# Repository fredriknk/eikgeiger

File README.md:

# EIKGEIGER

Eikgeiger opensource project for detection of background radiation in Norway. It is developed in cooperation with Eik Ideverksted. Use the design for anything you like comercially and privately, but i would love if you fork it so i can see what it is used for.

## First Batch
Thanks to [PCBway](www.pcbway.com) for providing assembled prototype units for this project. Its awesome that you support the opensource community like this! If you want one for yourself, i've made a [pcbway project](https://www.pcbway.com/project/shareproject/EikGeiger_IOT_Geigercounter_60bd1e1f.html) which you can make an assembly order quite easily. 

## Description
It uses an[ESP32-WROOM-32E](./DOCUMENTATION/esp32-wroom-32e_esp32-wroom-32ue_datasheet_en.pdf) wifi module both communication and MCU, and is mostly based on surface mount components.

Thanks to the DIYgeiger radmon project for inspiration [DIYGeiger RADMON + kit](https://sites.google.com/site/diygeigercounter/home/gk-radmon).

If you want to handsolder this, i really recommend to check out the awesome IBOM assembly utility (use it with a desktop as it sucks on mobile)
[Assembly IBOM](https://htmlpreview.github.io/?https://raw.githubusercontent.com/fredriknk/eikgeiger/main/PRODUCTION/eikgeiger-ibom.html)

[SCHEMATIC](./DOCUMENTATION/Opengieger_schematic.pdf)
## Specifications
| **Parameter**     | **Description**                                                     |
|-------------------|---------------------------------------------------------------------|
| _Input voltage_   | Usb-C cable, Header 4-6v, Direct 3.3v                               |
| _Current_         | Wifi: 150-250mA, Radio Off: 44mA, Only HV psup 4mA, Deep sleep 70uA |
| _Communication_   | 2.4ghz WIFI, Uart TTL, Uart over USB                                |
| _Baudrate_        | 115200                                                              |
| _PCB size_        | 31x119mm                                                            |
| _Case size_       | 30x35x121mm                                                         |
| _Series Resistor_ | 4.51MOHM                                                         |

## Serial port controll comands

To reconfigure device settings you need to connect the eikgeiger to a computer with a serial terminal (I reccomend to just use the [Arduino Program](https://www.arduino.cc/en/software), but any serial terminal should work)

When you want to configure a value you use two characters plus a number. So to set the PWM frequency to 2000hz, you would write PF2000 in the terminal and send. Some commands need a specific number, eg to factory reset you must transmit FR9999. after you have verified that the configuraion works you use SA1 to save the config to the flash eeprom

| **Characters**| **Unit**                | **Value** | **Factory Value** | **Description**                                                                                                                                                                                                                                           | **Example** |
|---------------|-------------------------|-----------|-------------------|-----------------------------------------------------------------------------------------------------------------------------------------------------------------------------------------------------------------------------------------------------------|-------------|
| VO            | _VOLT (value/4096 %)_   | 0-2000    | 350               | Set pwm duty cycle, this is a value which controlls the duty cycle of HV power supply, it is a 12bit (4096) value, but you cant go over 50% or the coil field colapses. So keep it under 2046=50% duty cycle. (SBM-20 tubes like it best between 350-400) | VO350       |
| VF            | _FREQUENCY (hz)_        | 0-18000   | 1001              | Set pwm frequency, from experimentation i have found ~1000hz to be most effective but it can make some coil whine, It is smart to not have this as a value divisible by log output, or it might generate some interferance with ADC readings              | VF1001      |
| SA            | _SAVE_                  | 1         | -                 | Saves parameters to eeprom                                                                                                                                                                                                                                | SA1         |
| RE            | _RESTART_               | 1         | -                 | Restarts device                                                                                                                                                                                                                                           | RE1         |
| RF            | _FACTORY RESET_         | 9999/1111 | -                 | Resets all values to factory default and restarts device, 1111 will reset all settings except wifi and radmon credentials, 9999 resets everything                                                                                                         | RF9999      |
| BE            | _BEEPER (activation)_   | 0/1       | 0                 | Activate beeper output 0=Off 1=On                                                                                                                                                                                                                         | BE1         |
| BD            | _BEEPER duty (val/255) _| 0-127     | 50                | Beeper duty cycle, higher number is louder                                                                                                                                                                                                                | BD50        |
| BF            | _BEEPER FREQUENCY (hz)_ | 10-40000  | 6000              | Beeper frequency 6000hZ is a very nice and annoying frequency                                                                                                                                                                                             | BF6000      |
| LE            | _LED (activation)_      | 0/1       | 1                 | Activate LED output 0=Off 1=On                                                                                                                                                                                                                            | LE1         |
| LF            | _FLASHTIME (mS)_        | 1-500     | 10                | How long the beeper beeps and led flashes in mS for every click. If value is higher than 60*1000/CPM, you will have counts without indication                                                                                                             | LF10        |
| LO            | _LOG OUTPUT_            | 0/1       | 1                 | Outputs  raw_volt:(Voltage ADC reading, arbtrary number not directly related to volt) set_volt:(Duty cycle value) cpmM:(Running average CPM for one minute) cpmH:(Running average CPM for one hour) cpm:(CPM value for last detection)                    | LO1         |
| LS            | _LOG SPEED_             | 0-10000   | 1000              | Number of milliseconds for every log output over serial    																																							                                      | LS1000      |
| EV            | _EVENTS (number)_       | 0-1000    | 0                 | How many events for one flash, in practice it will divide by that number, so a value of 10, it will need 10 detections for every led and ticker flash.                                                                                                    | EV0         |

## Description
The pcb has one pinheader (J5) which can be used for 1 x i2c or 2 x Onewire io,
and one header (J10) with 1xGpio, and 1x mosfet open collector for eg a clicker.
A piezo buzzer with 5mm pitch can be directly soldered in the header holes.
It is allso possible to split out the 5v from the usb to insert an ebay generic lipo charger/powersuply to make it battery driven with usb charging.

It allso implements an integrated FTDI chip to get serial over USB, 
and a transistor based rts#/dtr# pulldown function for the boot pin on the ESP 
(shamelessly stolen from the weemos d1 mini design) 
so it allows for automatic programming over USB without pushing the boot pin.

## Homeassistant Implementation
To add the sensor in home assistant, use the following YAML sensor, supplied by u/[chillinorway](https://github.com/chillinorway)
```
sensor:
  - platform: rest
    name: EIK_Geiger
    resource: http://<IP-Address>/cpm
    json_attributes:
      - "data"
    value_template: "OK"
  - platform: template
    sensors:
      cpm:
        value_template: "{{ state_attr('sensor.EIK_Geiger', 'data')['cpm'] }}"
        unit_of_measurement: "cpm"
      cpm_m:
        value_template: "{{ state_attr('sensor.EIK_Geiger', 'data')['cpm_M'] }}"
        unit_of_measurement: "cpm_avg_m"
      cpm_h:
        value_template: "{{ state_attr('sensor.EIK_Geiger', 'data')['cpm_H'] }}"
        unit_of_measurement: "cpm_avg_h"
      raw_volt:
        value_template: "{{ state_attr('sensor.EIK_Geiger', 'data')['raw_volt'] }}"
        unit_of_measurement: "raw_voltage"
```
## BUCK BOOST CONVERTER

It is designed for SBM-20 GM tube integrated onto the PCB with 6.3mm fuse holders, but it can use any tube up to 1000v if you just solder on some leads. The power supply is a standard buck boost, but with a 4x voltage multiplier output. It seems reaonably of effective, and consumes about 4ma@3.3v delivering 350v out running at 1000hz pwm. It has a voltage feedback read by adc2 on the esp32 module, but from experimentation i found it more stable to just set a pwm level rather than actively regulating it

## More Pictures
### Renders

### SBM-20 Enclosure

### SBM-19 Enclosure

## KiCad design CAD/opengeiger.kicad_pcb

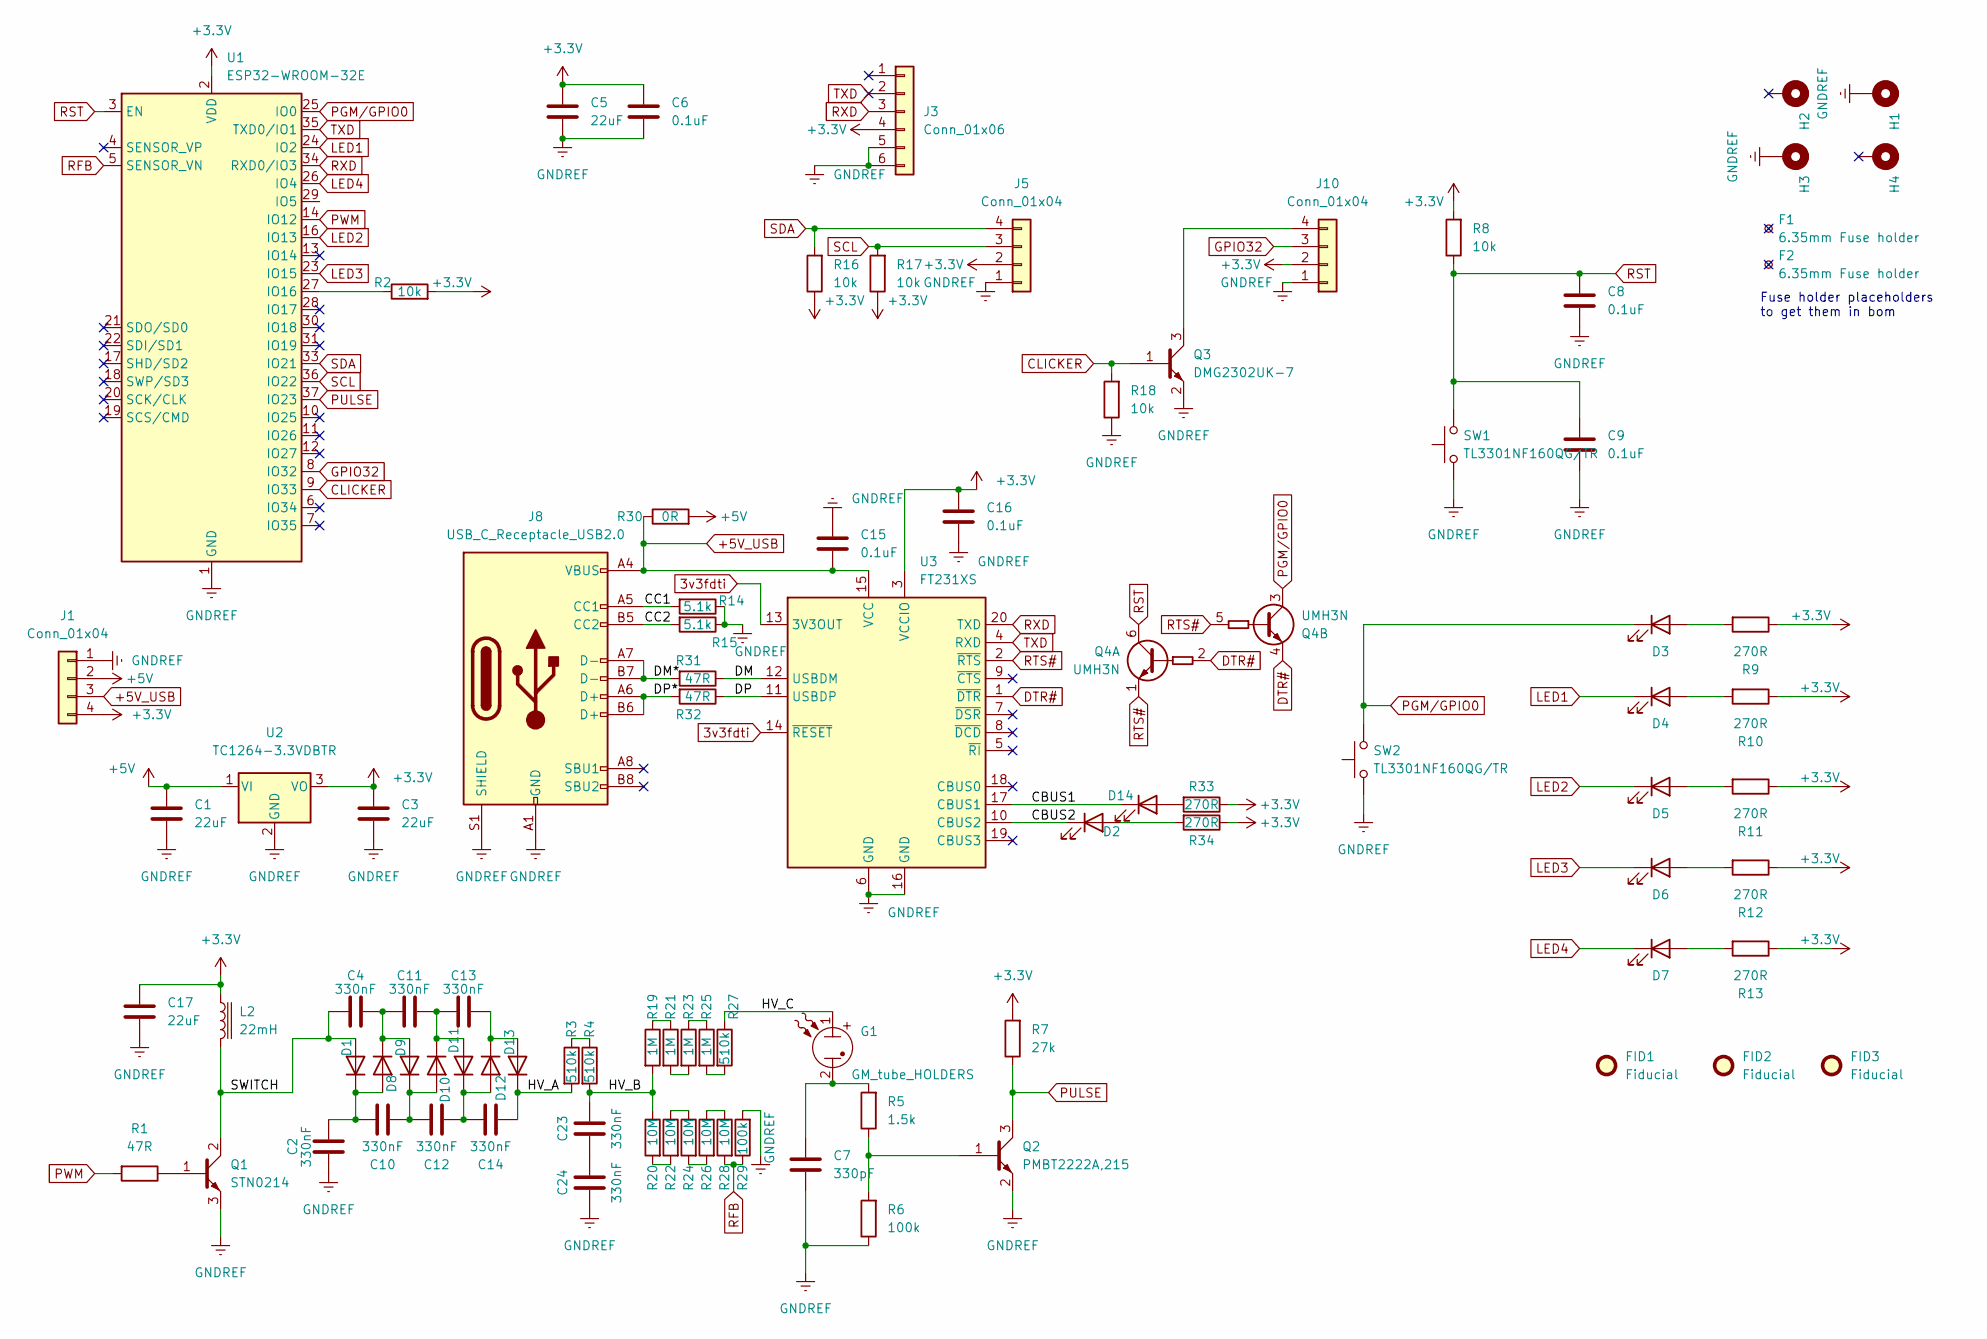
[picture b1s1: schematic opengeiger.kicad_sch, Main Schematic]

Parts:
C1, C3, C5, C17: 22uF; C_0805_2012Metric_Pad1.18x1.45mm_HandSolder; MPN CL21A226MOCLRNC; LCSC Part # C398815
C2, C4, C10, C11, C12, C13, C14, C23, C24: 330nF; C_1206_3216Metric_Pad1.33x1.80mm_HandSolder; MPN CL31B333KHHSFNE; LCSC Part # C710477
C6, C8, C9, C15, C16: 0.1uF; C_0603_1608Metric_Pad1.08x0.95mm_HandSolder; MPN CC0603KRX7R9BB104; LCSC Part # C14663
C7: 330pF; C_0603_1608Metric_Pad1.08x0.95mm_HandSolder; MPN CL10C331JB8NNNC; LCSC Part # C1664
D1, D8, D9, D10, D11, D12, D13: RS1J; D_SMA; MPN RS1J; LCSC Part # C434030
D2, D3, D4, D5, D6, D7, D14: RED_LED; LED_0603_1608Metric; MPN LTST-C191KRKT; LCSC Part # C2286
F1, F2: 6.35mm Fuse holder; FC-102-22; MPN FC-102 BRIGHT TIN; LCSC Part # C3206833
FID1, FID2, FID3: Fiducial; Fiducial_1mm_Mask2mm
G1: GM_tube_HOLDERS; SBM-20; MPN SBM-20
H1, H3: MountingHole_Pad; MountingHole_2.5mm_Pad_Via
H2, H4: MountingHole_Pad; MountingHole_2.5mm
J1, J5, J10: Conn_01x04; PinHeader_1x04_P2.54mm_Vertical; MPN 61300411121; LCSC Part # C2691448
J3: Conn_01x06; PinHeader_1x06_P2.54mm_Vertical; MPN 61300611121; LCSC Part # C37208
J8: USB_C_Receptacle_USB2.0; USB_C_Receptacle_HRO_TYPE-C-31-M-12; MPN CONN RCP USB2.0 TYP C 24P SMD RA; LCSC Part # C2765186
L2: 22mH; L_Radial_D10.5mm_P5.00mm_Abacron_AISR-01; MPN RLB1014-223KL; LCSC Part # C1330068
Q1: STN0214; SOT-223; MPN STN0214; LCSC Part # C2969811
Q2: PMBT2222A,215; SOT-23_Handsoldering; MPN PMBT2222A,215; LCSC Part # C23869
Q3: DMG2302UK-7; SOT-23_Handsoldering; MPN DMG2302UK-7; LCSC Part # C460977
Q4: UMH3N; SOT-363_SC-70-6; MPN UMH3N; LCSC Part # C62892
R1, R31, R32: 47R; R_0603_1608Metric_Pad0.98x0.95mm_HandSolder; MPN RMCF0603JT47R0; LCSC Part # C23182
R2, R8, R16, R17, R18: 10k; R_0603_1608Metric_Pad0.98x0.95mm_HandSolder; MPN RMCF0603JT10K0; LCSC Part # C25804
R3, R4, R27: 510k; R_1206_3216Metric_Pad1.30x1.75mm_HandSolder; MPN KTR18EZPJ514; LCSC Part # C17990
R5: 1.5k; R_0603_1608Metric_Pad0.98x0.95mm_HandSolder; MPN RNCP0603FTD1K50; LCSC Part # C22843
R6, R29: 100k; R_0603_1608Metric_Pad0.98x0.95mm_HandSolder; MPN RMCF0603JT100K; LCSC Part # C25803
R7: 27k; R_0603_1608Metric_Pad0.98x0.95mm_HandSolder; MPN RMCF0603JT27K0; LCSC Part # C22967
R9, R10, R11, R12, R13, R33, R34: 270R; R_0603_1608Metric_Pad0.98x0.95mm_HandSolder; MPN RC0603JR-07270RL; LCSC Part # C22966
R14, R15: 5.1k; R_0603_1608Metric_Pad0.98x0.95mm_HandSolder; MPN RMCF0603JT5K10; LCSC Part # C23186
R19, R21, R23, R25: 1M; R_1206_3216Metric_Pad1.30x1.75mm_HandSolder; MPN KTR18EZPF1004; LCSC Part # C253347
R20, R22, R24, R26, R28: 10M; R_1206_3216Metric_Pad1.30x1.75mm_HandSolder; MPN KTR18EZPF1005; LCSC Part # C2075848
R30: 0R; R_1206_3216Metric_Pad1.30x1.75mm_HandSolder; MPN KTR18EZPF0; LCSC Part # C17888
SW1, SW2: TL3301NF160QG/TR; SW_TL3301NF160QG_TR; MPN TL3301NF160QG/TR; LCSC Part # C255812
U1: ESP32-WROOM-32E; ESP32-WROOM-32; MPN ESP32-WROOM-32E-N16; LCSC Part # C701343
U2: TC1264-3.3VDBTR; SOT-223-3_TabPin2; MPN TC1264-3.3VDBTR; LCSC Part # C6186
U3: FT231XS; SSOP-20_3.9x8.7mm_P0.635mm; MPN FT231XS; LCSC Part # C132160

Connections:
3v3fdti: U3.13 (3V3OUT), U3.14 (~RESET)
+3.3V: C3.1, C5.1, C6.1, C16.1, C17.1, J1.4, J3.4, J5.2, J10.2, L2.1, R2.2, R7.2, R8.2, R9.1, R10.1, R11.1, R12.1, R13.1, R16.1, R17.1, R33.1, R34.1, U1.2 (VDD), U2.3 (VO), U3.3 (VCCIO)
+5V: C1.1, J1.2, R30.2, U2.1 (VI)
+5V_USB: C15.2, J1.3, J8.A4 (VBUS), J8.A9 (VBUS), J8.B4 (VBUS), J8.B9 (VBUS), R30.1, U3.15 (VCC)
/CBUS1: D14.1 (K), U3.17 (CBUS1)
/CBUS2: D2.1 (K), U3.10 (CBUS2)
/CC1: J8.A5 (CC1), R14.2
/CC2: J8.B5 (CC2), R15.2
/DM: R31.1, U3.12 (USBDM)
/DM*: J8.A7 (D-), J8.B7 (D-), R31.2
/DP: R32.1, U3.11 (USBDP)
/DP*: J8.A6 (D+), J8.B6 (D+), R32.2
/HV_A: C14.2, D13.1 (K), R3.2
/HV_B: C23.2, R4.2, R19.2, R20.1
/HV_C: G1.1, R27.1
/SWITCH: C4.1, D1.2 (A), L2.2, Q1.2 (C), Q1.4 (C)
CLICKER: Q3.1 (B), R18.2, U1.9 (IO33)
DTR#: Q4.2 (B1), Q4.4 (E2), U3.1 (~DTR)
GNDREF: C1.2, C2.1, C3.2, C5.2, C6.2, C7.2, C8.2, C9.2, C15.1, C16.2, C17.2, C24.1, H1.1, H3.1, J1.1, J3.5, J3.6, J5.1, J8.A1 (GND), J8.A12 (GND), J8.B1 (GND), J8.B12 (GND), J8.S1 (SHIELD), J10.1, Q1.3 (E), Q2.2 (E), Q3.2 (E), R6.1, R14.1, R15.1, R18.1, R29.2, SW1.1, SW2.1, U1.1 (GND), U1.15 (GND), U1.38 (GND), U1.39 (GND), U2.2 (GND), U3.6 (GND), U3.16 (GND)
GPIO32: J10.3, U1.8 (IO32)
LED1: D4.1 (K), U1.24 (IO2)
LED2: D5.1 (K), U1.16 (IO13)
LED3: D6.1 (K), U1.23 (IO15)
LED4: D7.1 (K), U1.26 (IO4)
unnamed: C7.1, G1.2, R5.2
unnamed: C23.1, C24.2
unnamed: C2.2, C10.1, D1.1 (K), D8.2 (A)
unnamed: D2.2 (A), R34.2
unnamed: D3.2 (A), R9.2
unnamed: D4.2 (A), R10.2
unnamed: D5.2 (A), R11.2
unnamed: D6.2 (A), R12.2
unnamed: D7.2 (A), R13.2
unnamed: C4.2, C11.1, D8.1 (K), D9.2 (A)
unnamed: C10.2, C12.1, D9.1 (K), D10.2 (A)
unnamed: C11.2, C13.1, D10.1 (K), D11.2 (A)
unnamed: C12.2, C14.1, D11.1 (K), D12.2 (A)
unnamed: C13.2, D12.1 (K), D13.2 (A)
unnamed: D14.2 (A), R33.2
unnamed: J10.4, Q3.3 (C)
unnamed: Q1.1 (B), R1.1
unnamed: Q2.1 (B), R5.1, R6.2
unnamed: R3.1, R4.1
unnamed: R19.1, R21.1
unnamed: R20.2, R22.2
unnamed: R21.2, R23.2
unnamed: R22.1, R24.1
unnamed: R23.1, R25.1
unnamed: R24.2, R26.2
unnamed: R25.2, R27.2
unnamed: R26.1, R28.1
unnamed: R2.1, U1.27 (IO16)
PGM/GPIO0: D3.1 (K), Q4.3 (C2), SW2.2, U1.25 (IO0)
PULSE: Q2.3 (C), R7.1, U1.37 (IO23)
PWM: R1.2, U1.14 (IO12)
RFB: R28.2, R29.1, U1.5 (SENSOR_VN)
RST: C8.1, C9.1, Q4.6 (C1), R8.1, SW1.2, U1.3 (EN)
RTS#: Q4.1 (E1), Q4.5 (B2), U3.2 (~RTS)
RXD: J3.3, U1.34 (RXD0/IO3), U3.20 (TXD)
SCL: J5.3, R17.2, U1.36 (IO22)
SDA: J5.4, R16.2, U1.33 (IO21)
TXD: J3.2, U1.35 (TXD0/IO1), U3.4 (RXD)

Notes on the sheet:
Fuse holder placeholders to get them in bom

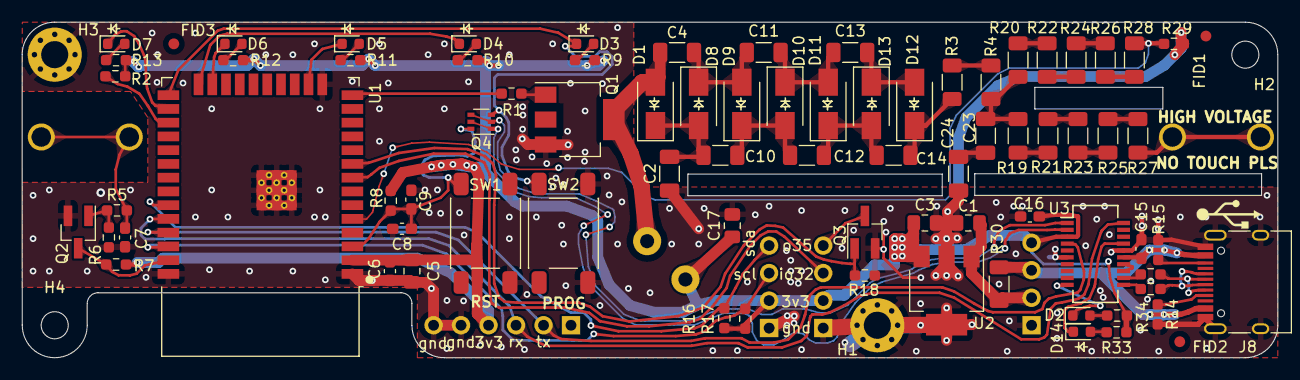
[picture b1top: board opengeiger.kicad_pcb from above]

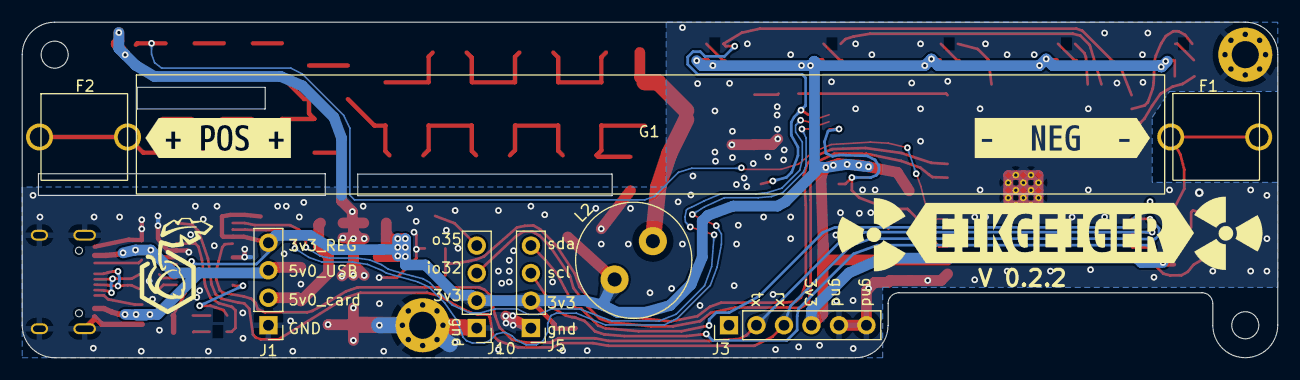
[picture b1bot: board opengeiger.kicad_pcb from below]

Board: 2 copper layers, 116.0 x 31.0 mm, 95 parts (11 on the bottom side), 62 nets.

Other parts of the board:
kibuzzard-637F3F6B: G***; kibuzzard-637F3F6B
kibuzzard-6571CD20: G***; kibuzzard-6571CD20
kibuzzard-6571CD43: G***; kibuzzard-6571CD43

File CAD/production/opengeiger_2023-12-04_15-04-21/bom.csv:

Designator,Footprint,Quantity,Value,LCSC Part #
"C1, C17, C3, C5",0805,4,22uF,CL21A226MOCLRNC
"C10, C11, C12, C13, C14, C2, C23, C24, C4",1206,9,330nF,CL31B333KHHSFNE
"C15, C16, C6, C8, C9",0603,5,0.1uF,06035C104KAT4A
C7,0603,1,330pF,CC0603KRX7R9BB331
"D1, D10, D11, D12, D13, D8, D9",D_SMA,7,RS1J,RS1J
"D14, D2, D3, D4, D5, D6, D7",0603,7,0603RBD0700S01,0603RBD0700S01
"FID1, FID2, FID3",Fiducial_1mm_Mask2mm,3,Fiducial,
G1,SBM-20,1,GM_tube_HOLDERS,
"H1, H3",MountingHole_2.5mm_Pad_Via,2,MountingHole_Pad,
"H2, H4",MountingHole_2.5mm,2,MountingHole_Pad,
"J1, J10, J5",PinHeader_1x04_P2.54mm_Vertical,3,Conn_01x04,61300411121
J3,PinHeader_1x06_P2.54mm_Vertical,1,Conn_01x06,61300611121
J8,USB_C_Receptacle_HRO_TYPE-C-31-M-12,1,USB_C_Receptacle_USB2.0,CONN RCP USB2.0 TYP C 24P SMD RA
L2,L_Radial_D10.5mm_P5.00mm_Abacron_AISR-01,1,22mH,RLB1014-223KL
Q1,SOT-223,1,STN0214,STN0214
Q2,SOT-23_Handsoldering,1,"PMBT2222A,215","PMBT2222A,215"
Q3,SOT-23_Handsoldering,1,DMG2302UK-7,DMG2302UK-7
Q4,SOT-363_SC-70-6,1,UMH3N,
"R1, R31, R32",0603,3,47R,RMCF0603JT47R0
"R10, R11, R12, R13, R33, R34, R9",0603,7,270R,RC0603JR-07270RL
"R14, R15",0603,2,5.1k,RMCF0603JT5K10
"R16, R17, R18, R2, R8",0603,5,10k,RMCF0603JT10K0
"R19, R21, R23, R25",1206,4,1M,KTR18EZPF1004
"R20, R22, R24, R26, R28",1206,5,10M,KTR18EZPF1005
"R27, R3, R4",1206,3,510k,KTR18EZPJ514
"R29, R6",0603,2,100k,RMCF0603JT100K
R30,1206,1,0R,KTR18EZPF0
R5,0603,1,1.5k,RNCP0603FTD1K50
R7,0603,1,27k,RMCF0603JT27K0
"SW1, SW2",SW_TL3301NF160QG_TR,2,TL3301NF160QG/TR,TL3301NF160QG/TR
U1,ESP32-WROOM-32,1,ESP32-WROOM-32E,ESP32-WROOM-32E-N16
U2,SOT-223-3_TabPin2,1,TC1264-3.3VDBTR,TC1264-3.3VDBTR
U3,SSOP-20_3.9x8.7mm_P0.635mm,1,FT231XS,

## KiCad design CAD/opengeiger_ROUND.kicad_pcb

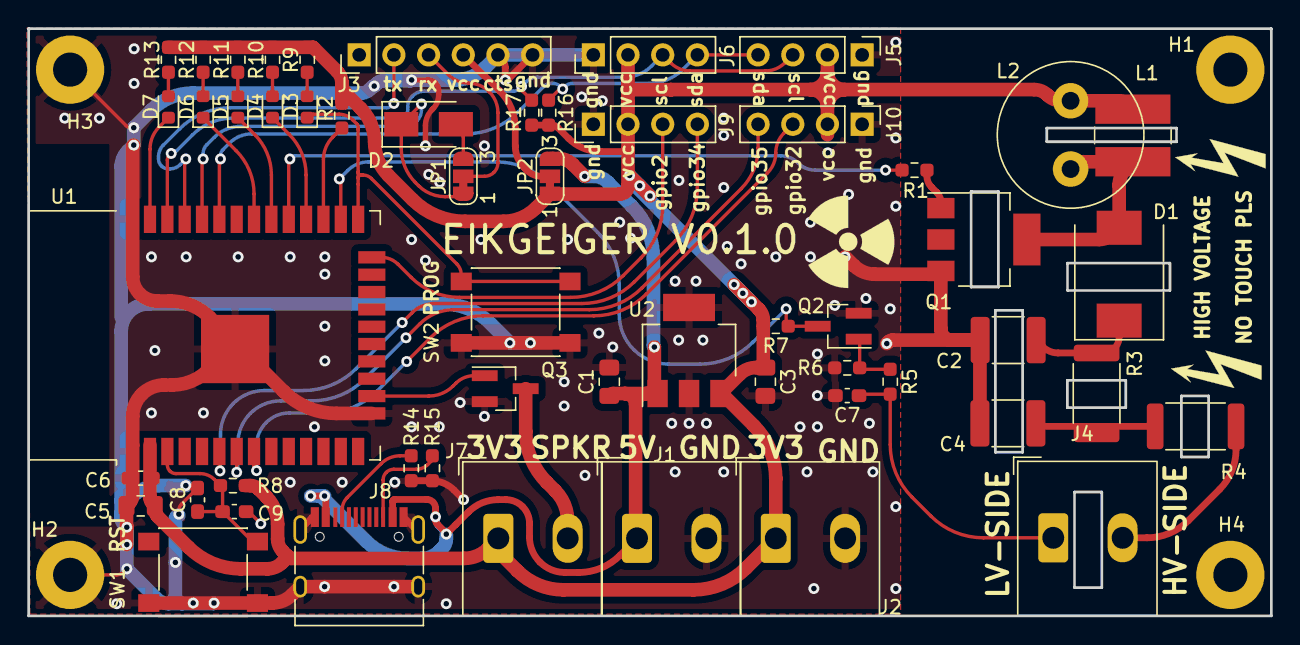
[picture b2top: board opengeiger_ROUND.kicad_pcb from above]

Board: 2 copper layers, 91.0 x 43.0 mm, 58 parts (0 on the bottom side), 39 nets.

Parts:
C1, C3, C5: 22uF; C_0805_2012Metric_Pad1.18x1.45mm_HandSolder
C2, C4: 0.01uF/1kV; C_1812_4532Metric
C6, C8, C9: 0.1uF; C_0603_1608Metric_Pad1.08x0.95mm_HandSolder
C7: 330pF; C_0603_1608Metric_Pad1.08x0.95mm_HandSolder
D1: STTH212S; D_SMC
D2: VS-E7MH0112HM3/I; D_SMA
D3, D4, D5, D6, D7: 0603RBD0700S01; LED_0603_1608Metric
H1, H2, H3, H4: MountingHole_Pad; MountingHole_2.5mm_Pad
J1, J2, J4, J7: Conn_01x02; TB010-508-02BE
J3: Conn_01x06; PinHeader_1x06_P2.54mm_Vertical
J5, J6, J9, J10: Conn_01x04; PinHeader_1x04_P2.54mm_Vertical
J8: USB_C_Receptacle_USB2.0; USB_C_Receptacle_HRO_TYPE-C-31-M-12
JP1, JP2: SolderJumper_3_Bridged12; SolderJumper-3_P1.3mm_Bridged12_RoundedPad1.0x1.5mm_NumberL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
L1: SDR0503-153JL; L_TracoPower_TCK-047_5.2x5.8mm
L2: RLB1314-153KL; L_Radial_D10.5mm_P5.00mm_Abacron_AISR-01
Q1: STN0214; SOT-223
Q2, Q3: PMBT2222A,215; SOT-23_Handsoldering
R1: 47R; R_0603_1608Metric_Pad0.98x0.95mm_HandSolder
R2, R8, R16, R17: 10k; R_0603_1608Metric_Pad0.98x0.95mm_HandSolder
R3: 1M; R_2512_6332Metric
R4: 4.7M; R_2512_6332Metric
R5: 1.5k; R_0603_1608Metric_Pad0.98x0.95mm_HandSolder
R6: 100k; R_0603_1608Metric_Pad0.98x0.95mm_HandSolder
R7: 27k; R_0603_1608Metric_Pad0.98x0.95mm_HandSolder
R9, R10, R11, R12, R13: 270R; R_0603_1608Metric_Pad0.98x0.95mm_HandSolder
R14, R15: 5.1k; R_0603_1608Metric_Pad0.98x0.95mm_HandSolder
SW1, SW2: TL3301NF160QG/TR; SW_SPST_PTS645
U1: ESP32-WROOM-32E; ESP32-WROOM-32
U2: AP7361C-33E; SOT-223-3_TabPin2

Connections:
+3.3V: C3.1, C5.1, C6.1, J2.1, J5.2, J6.2, J7.1, J9.2, J10.2, JP2.1 (A), L1.1, L2.1, R2.2, R7.2, R8.2, R9.1, R10.1, R11.1, R12.1, R13.1, R16.1, R17.1, U1.2 (VDD), U2.3 (VO)
+5V: C1.1, J1.1, J8.A4 (VBUS), J8.A9 (VBUS), J8.B4 (VBUS), J8.B9 (VBUS), JP2.3 (B), U2.1 (VI)
CLICKER: Q3.1 (B), U1.16 (IO13)
GNDREF: C1.2, C2.2, C3.2, C4.2, C5.2, C6.2, C7.2, C8.2, C9.2, H2.1, H3.1, J1.2, J2.2, J3.5, J3.6, J5.1, J6.1, J8.A1 (GND), J8.A12 (GND), J8.B1 (GND), J8.B12 (GND), J8.S1 (SHIELD), J9.1, J10.1, Q1.3 (E), Q2.2 (E), Q3.2 (E), R6.1, R14.1, R15.1, SW1.1, SW2.1, U1.1 (GND), U1.15 (GND), U1.38 (GND), U1.39 (GND), U2.2 (GND)
GPIO02: J9.3, U1.24 (IO2)
GPIO32: J10.3, U1.8 (IO32)
GPIO34: J9.4, U1.6 (IO34)
GPIO35: J10.4, U1.7 (IO35)
LED1: D4.1 (K), U1.28 (IO17)
LED2: D5.1 (K), U1.30 (IO18)
LED3: D6.1 (K), U1.31 (IO19)
LED4: D7.1 (K), U1.37 (IO23)
unnamed: C2.1, D1.1 (K), R3.1
unnamed: C4.1, R3.2, R4.1
unnamed: C7.1, J4.1, R5.2
unnamed: D1.2 (A), L1.2, L2.2, Q1.4 (C)
unnamed: D2.2 (A), JP1.3 (B)
unnamed: D3.2 (A), R9.2
unnamed: D4.2 (A), R10.2
unnamed: D5.2 (A), R11.2
unnamed: D6.2 (A), R12.2
unnamed: D7.2 (A), R13.2
unnamed: J4.2, R4.2
unnamed: J7.2, Q3.3 (C)
unnamed: J8.A5 (CC1), R14.2
unnamed: J8.B5 (CC2), R15.2
unnamed: Q1.1 (B), R1.1
unnamed: Q2.1 (B), R5.1, R6.2
unnamed: R2.1, U1.27 (IO16)
PGM/GPIO0: D3.1 (K), SW2.2, U1.25 (IO0)
PULSE: Q2.3 (C), R7.1, U1.26 (IO4)
PWM: R1.2, U1.29 (IO5)
RST: C8.1, C9.1, R8.1, SW1.2, U1.3 (EN)
RX5V: J3.3, JP1.2 (C)
RXD: D2.1 (K), JP1.1 (A), U1.34 (RXD0/IO3)
SCL: J5.3, J6.3, R17.2, U1.36 (IO22)
SDA: J5.4, J6.4, R16.2, U1.33 (IO21)
TXD: J3.2, U1.35 (TXD0/IO1)
VIN: J3.4, JP2.2 (C)

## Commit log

2022-11-03 Feat: Readme and gitignore
2022-11-03 Feat: First repo push, JLC prod
2022-11-03 Feat: Added 3d models and did a new export
2022-11-03 FEAT: Added new picture and updated readme
2022-11-03 Feat: Updated readme with SBM-2Feat: Updated readme with SBM-200
2022-11-03 Feat:Added schematics, and updated readme
2022-11-03 Feat: Added schematic link in readme
2022-11-03 Feat: Added main picture and updated readme
2022-11-03 fix: Readme update
2022-11-03 Fix: Delete backup file
2022-11-03 fix: Delete file wrong location
2022-11-03 Feat: added licence
2022-11-21 feat: added interactive html bom
2022-11-21 feat: 1206 version
2022-11-22 Feat: Slimmify board
2022-11-23 Feat: Slimmify more and usb uart
2022-11-24 Feat:WIP Rounding tracks
2022-11-24 Feat:Round Corners, temp gerber production
2022-11-25 Feat: Production files for JLC prod, readme update
2022-11-25 Feat: html bom and added prod csv files
2022-11-25 Fix: Ibom Export
2022-11-25 Feat: Readme update new features
2022-11-30 Feat:Code folder and charge pump simulation
2022-12-06 feat: added firmware VSCODE project
2022-12-07 FEAT:PID reg wip
2022-12-08 Feat: PWM pid
2022-12-09 Feat: New prod, working code
2022-12-09 Feat: Fixed adc port and captive portal
2022-12-09 Fix: Added autosave folder to gitignore
2022-12-10 Feat: Got rid of pid
2022-12-11 Feat: New order from jlcpcb rev 0.2.1
2022-12-11 Feat:Updated Pictures
2022-12-11 Feat:Updated schematic revnr and pdfprint and pict
2022-12-12 Feat: Readme and licensing
2022-12-12 Fix: Readme formatting
2022-12-12 Fix: Case link
2022-12-14 feat: Serial controll and eeprom settings
2022-12-15 Feat: Added help menu, fixed readme error
2022-12-29 Feat: Added post handlder
2022-12-30 Feat:Wifi connection first working proto
2022-12-30 Feat: First Fully Functional code
2022-12-30 Fix: Formatted JSON output
2022-12-30 Fix: Removed two unused text inputs in ap
2023-01-01 Feat: Added persistant data to AP screen
2023-01-06 Feat: Added network reconnect
2023-01-16 feat: Add explain helper, and map it to ?
2023-01-23 Fix: Small additions to "?" merger
2023-02-09 Feat: Added yaml config to readme
2023-02-09 Fix:Readme formatting
2023-11-30 Licencing change
2023-11-30 Feat: Updated default value in help
2023-12-01 Feat:Printing macaddress
2023-12-04 Feat: Added LCSC part numbers to schematics
2023-12-06 Feat: New 3d models
2023-12-07 Feat: New pictures for V0.2.1
2023-12-07 Fix: Readme fix
2023-12-07 Fix: Readme
2023-12-07 Feat: Update to 0.2.2
2023-12-07 Feat: Cleanup in enclosures
2023-12-07 Feat: Fixed wrong pin assignment for beeper
2024-01-11 Schematic prettify
